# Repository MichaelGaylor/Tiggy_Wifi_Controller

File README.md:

# Tiggy WiFi CNC Motion Controller

Open-source ESP32 **6-axis** CNC motion controller firmware with LinuxCNC and GRBL support. Free and fully functional for all 6 axes with LinuxCNC, GRBL senders, or any G-code host. Mach3 support available separately.

Replaces parallel port drivers with a WiFi or Ethernet-connected motion controller supporting up to 6 axes, spindle encoder feedback, and expanded I/O. Works standalone (GRBL-compatible serial/telnet), with LinuxCNC, or with Mach3 (plugin sold separately). **All 6 axes are free and open source** -- the only limitation is in the Mach3 plugin, which requires a Pro Mach3 license for axes 4-6.

## Downloads

| Component | Download | Description |
|-----------|----------|-------------|
| **ESP32 Firmware** | [Flash from browser](https://michaelgaylor.github.io/Tiggy_Wifi_Controller/) | One-click web flasher (Chrome/Edge) |
| **LinuxCNC** | [Tiggy-LinuxCNC.tar.gz](https://github.com/MichaelGaylor/Tiggy_Wifi_Controller/releases/latest/download/Tiggy-LinuxCNC.tar.gz) | Driver, installer and set-up wizard |
| **Mach3 Plugin** | [www.tiggyengineering.com](https://www.tiggyengineering.com) | Windows plugin (free: 3-axis, Pro: 6-axis) |
| **Protocol Tester** | [TiggyProtocolTester.exe](https://github.com/MichaelGaylor/Tiggy_Wifi_Controller/releases/latest/download/TiggyProtocolTester.exe) | Windows GUI for testing and configuring |

Firmware and LinuxCNC builds are created automatically via GitHub Actions.

## Features

- Up to **6 axes** (X, Y, Z, A, B, C) with independent step/direction control
- **WiFi or Ethernet** (W5500) connectivity -- auto-detected, no configuration needed
- Motion streamed from the host as timed segments with acknowledgement: evenly spaced pulses, and lost or repeated packets can never lose or repeat a step
- Safe when the host goes away: host watchdog, jog deadman, outputs off on E-stop
- GRBL-compatible serial/telnet interface for standalone use
- Homing, limit switches, E-stop and probe inputs, handled in the controller
- Spindle on/off or PWM, charge pump, auxiliary outputs and inputs (count varies by board)
- Spindle speed feedback from an encoder or a one-pulse-per-revolution sensor
- **Screw cutting on lathes**: the controller itself keeps the tool in step with the spindle, so the pitch holds when the spindle slows in the cut and every pass follows the last
- Optional **I/O expansion module** (pendant buttons, relay outputs)
- Auto-discovery and automatic reconnection

## Supported Hardware

| Board | MCU | Wired Axes | Notes |
|-------|-----|------------|-------|
| Tiggy Standard board | ESP32-S3-Zero (FH4R2) | 3 (X/Y/Z) | Compact, Quad SPI PSRAM |
| Tiggy Pro board (Octal) | ESP32-S3-DevKitC-1 (N16R8/N8R8) | 6 (X/Y/Z/A/B/C) | Octal SPI PSRAM, limited I/O |
| Tiggy Pro board (Quad) | ESP32-S3-DevKitC-1 (N8/N8R2) | 6 (X/Y/Z/A/B/C) | Quad SPI PSRAM, more I/O |
| Classic board | ESP32-WROOM-32 | 6 (limited I/O) | Legacy support |

All boards run the same 6-axis firmware. "Wired Axes" refers to the number of step/dir GPIO pairs physically routed on the board. The firmware supports 6 axes regardless of board -- unused axes simply have no GPIO assigned.

One setting trades the B and C axes of the six-axis boards for inputs and outputs - a spindle sensor, a charge pump, more auxiliary I/O: see [Four axes and more I/O](#four-axes-and-more-io-spindle-sensor-and-screw-cutting).

## Quick Start

### Flash Firmware

**Easiest:** Open the [Web Flasher](https://michaelgaylor.github.io/Tiggy_Wifi_Controller/) in Chrome or Edge, plug in your ESP32 via USB, select your board, and click Flash. No software install needed.

**From source** (requires [PlatformIO](https://platformio.org/)):

```bash
cd firmware
pio run -e esp32s3-devkitc -t upload    # Tiggy Pro board (6 wired axes)
pio run -e esp32s3-zero -t upload       # Tiggy Standard board (3 wired axes)
```

### LinuxCNC

```bash
sudo apt install linuxcnc-uspace linuxcnc-uspace-dev   # already there on the LinuxCNC live image
tar xzf Tiggy-LinuxCNC.tar.gz
cd linuxcnc-package
./install.sh    # builds the driver, then starts the set-up program
```

Or double-click `install.desktop` from your file manager.

The set-up program ("Tiggy set-up for LinuxCNC" in the menu afterwards) finds the controller on the network and sets up a mill, router or lathe with it connected, in the manner of Mach3's Config menu: which axis each motor output drives, motor tuning with the motor running from the page, switches with a lamp for each input, the spindle and its sensor. It writes a complete configuration to `~/linuxcnc/configs` and starts LinuxCNC with it. No realtime kernel is needed: LinuxCNC plans the motion and the controller makes the step pulses. What to expect, and every pin and setting of the `tiggy` driver, is in [linuxcnc/README.md](linuxcnc/README.md).

### Mach3 (Windows)

Download the Mach3 plugin from [www.tiggyengineering.com](https://www.tiggyengineering.com), then:

1. Copy `Tiggy.dll` to `C:\Mach3\PlugIns\` and `M62-M65.m1s` to `C:\Mach3\macros\Mach3Mill\`
2. Start Mach3 and choose **Tiggy Motion Controller** as the motion device
3. Set the machine up in Mach3's own Config menu (Motor Tuning, Ports and Pins, Homing/Limits) -- the plugin finds the controller by itself

Plugin 2.0 needs controller firmware 1.2.0 or newer. See the [User Manual](Tiggy_Plugin_Manual.md).

**Free tier**: 3 axes (X/Y/Z). **Pro Mach3 license**: 6 axes, slaved axes, I/O expansion module, screw cutting (G32/G76 in Mach3 Turn). Note: this axis limit applies **only to the Mach3 plugin**. LinuxCNC, GRBL senders, and all other host software get full 6-axis support for free.

## Four axes and more I/O: spindle sensor and screw cutting

Six axes use nearly every terminal of a Tiggy Pro board. A lathe that cuts threads, and many a mill, would rather have four axes and the inputs and outputs. Setting the controller's *machine layout* to **four axes** (configuration key `WCNC_CFG_MACHINE_LAYOUT`; in Mach3 it is on the plugin's Terminals tab) keeps X, Y, Z and A - and Ethernet - and turns the terminals of B and C into inputs and outputs. The same set-up serves a lathe and a mill: the spindle sensor takes only the inputs its kind needs, and every sensor terminal it leaves free is an auxiliary input.

With four axes ("or" = what the terminal is when the sensor does not use it):

| | Tiggy Pro (octal memory) | Tiggy Pro (quad memory) |
|---|---|---|
| Encoder A | GPIO 16, or auxiliary input 3 | GPIO 16, or auxiliary input 4 |
| Encoder B | GPIO 17, or auxiliary input 4 | GPIO 17 |
| Index pulse / single sensor | GPIO 21, or auxiliary input 2 | GPIO 37 |
| Other auxiliary inputs | 1: GPIO 18 | 1 to 3: GPIO 18, 21, 36 |
| Auxiliary outputs | 1 to 3: GPIO 11, 12, 40 | 1 to 5: GPIO 11, 12, 40, 39, 34 |
| Charge pump | GPIO 39 | GPIO 10 |

So an octal-memory Pro board with four axes, Ethernet and an encoder with index still has a limit/home input per axis, probe, E-stop, an auxiliary input, the spindle output, a charge pump and three auxiliary outputs; without a sensor it has four auxiliary inputs. No terminal changes between input and output with the sensor setting - the sensor only ever shares a terminal with an input - so a sensor left wired while the setting is changed is never driven against. A single sensor has its terminal even with six axes on both Pro boards (GPIO 21 and GPIO 37). The Tiggy Standard board has its sensor terminals in any case (encoder A / B / index on GPIO 15 / 16 / 17; those the sensor does not use are auxiliary inputs 1 to 3). `firmware/test/test_pin_layout.c` checks every combination for each board and prints it.

The spindle sensor is either an **encoder with A and B channels**, with or without an index pulse (100 lines or more), or a **single sensor giving one pulse per revolution**, which goes on the index terminal. The encoder gives the better thread: with one pulse per turn the controller cannot see a change of spindle speed until the turn is over. (A single sensor giving several pulses per revolution serves the speed display only: nothing tells the pulses apart, so no thread can be started by them.) The inputs have the chip's weak pull-ups: a single sensor that switches to ground connects directly, but an open-collector encoder needs pull-up resistors of its own (a few kilohms to 3.3 V) to be read at speed, or push-pull outputs.

A threading pass is played in step with the spindle or not at all. If something breaks into one - a feed hold or stop from the host in the middle of it, the host leaving the controller without motion, a spindle the axes cannot keep up with - the controller brings the axes to rest, drops what was left and says so (`WCNC_STREAM_SYNC_LOST`), rather than carry on out of step with the thread already cut.

Screw cutting is available to both hosts: G32 and G76 in Mach3 Turn through the plugin, G33 and G76 in LinuxCNC through its driver (`linuxcnc/README.md`).

For screw cutting the host streams the threading pass like any other move, marked to be played *by the spindle* and to begin at its index (`WCNC_SEG_FLAG_SPINDLE_SYNC`, `WCNC_SEG_FLAG_INDEX_START` in `protocol/wifi_cnc_protocol.h`). The controller then advances through the move by the angle the spindle really turns, so the pitch does not depend on the spindle holding its speed, a spindle that stalls stops the axes with it, and every pass begins at the same place on the work. The Mach3 plugin does this for G32 and G76 in Mach3 Turn, the LinuxCNC driver for G33 and G76.

### A carrier board for either layout

[`hardware/devkitc-carrier`](hardware/devkitc-carrier) is a KiCad project for a board that an ESP32-S3-DevKitC-1 plugs into. It has plugs for six drives, and four jumpers that give the pins of B and C either to their drives (six axes) or to three relays and the charge pump (four axes). Also on it: a socket for a W5500 Ethernet module, seven opto-isolated inputs (limits, E-stop, probe), a separate plug for the spindle sensor and a 0 to 10 V spindle speed output. It is revision A and has not been built yet - see its README before ordering one.

## Architecture

```
Mach3 / LinuxCNC / Serial Terminal
              |
         [TCP:58429 + UDP:58427/58428]
              |
        ESP32-S3 Firmware (this repo)
              |
        Step/Dir/Enable/Spindle/IO GPIO
```

- **TCP** (port 58429): Handshake, configuration, keep-alive
- **UDP** (port 58427): Motion stream, jog, home, outputs, E-stop; status reports go back to the host
- **Protocol**: Defined in `protocol/wifi_cnc_protocol.h` (version 1.2)

## Testing without hardware

The firmware's motion code (`firmware/main/motion`) is plain C that also builds on a PC, where it runs behind the real network ports with a simulated machine attached:

```bash
firmware/test/pc/build.sh                 # or build.bat on Windows: builds the test library, runs the unit test
python tools/firmware_sim.py              # the firmware's motion code as a controller on this PC
python tools/protocol_conformance.py --sim --motion 127.0.0.1    # protocol tests
python tools/firmware_selftest.py         # G-code mode moves, feed hold, homing, older hosts, starved stream, pulse spacing
python tools/threading_test.py            # screw cutting: every step of a pass against the angle of a simulated spindle
python tools/encoder_bench_test.py 127.0.0.1 --lines 1024 --sim    # the bench test of a real encoder (below), the simulator turning one
python tools/encoder_loopback_test.py 127.0.0.1 --sim              # the board's test of its own encoder inputs (below), on the simulator
python tools/ugs_compat_test.py           # TiggyUGS's own connection, planner and sender code against the firmware
                                          # (needs TiggyUGS's source and its Python packages: see the file)
```

Host software (the Mach3 plugin, LinuxCNC, TiggyUGS) connects to it like to a board. Hosts written for protocol 1.0 or 1.1 keep working with firmware 1.2: their speed-described segments are played as before, the status report shows them the room in the queue those wait in, and their reset packet stops and drops what they sent. `tools/tiggy_sim.py` is an independent model of the same protocol in Python; the conformance tests hold both to one behaviour, and can be run against a real board too (`protocol_conformance.py <ip>`, add `--motion` only when the motors are free to move).

The LinuxCNC driver is tested the same way. It builds, unchanged, around a stand-in for LinuxCNC and is run against the firmware simulator (it starts its own simulators, so close one you started by hand first):

```bash
linuxcnc/test/build.sh                    # or build.bat on Windows
python tools/linuxcnc_driver_test.py      # moves to the step, packet loss, a stalling PC, E-stop, limits, reconnection
linuxcnc/test/run_in_linuxcnc.sh          # the same driver inside a real LinuxCNC (Linux with linuxcnc-uspace-dev):
                                          # a mill, home switches, G33, and a lathe with G33 and a G76 cycle (also at 150 rpm by a one-pulse sensor)
xvfb-run -a python3 linuxcnc/test/config_test.py     # the set-up program, worked from its pages against the simulator
```

### With a board on the bench

A bare dev board is enough; nothing needs to be wired to it.

```bash
python tools/protocol_conformance.py <ip> --motion    # the binary protocol over the network (the axes "move": no motors, or a free machine)
python tools/grbl_serial_test.py COM14                # the G-code interface on the USB port: moves, arcs, hold, jog and jog cancel, reset, no drift
python tools/grbl_serial_test.py <ip>                 # the same interface over the network (telnet, port 23)
python tools/ugs_serial_test.py COM14                 # TiggyUGS's own serial connection and sender against it (needs TiggyUGS's source)
python tools/latency_test.py <ip>                     # how promptly the controller answers over the network: median and worst case
linuxcnc/test/run_on_board.sh <ip> --motion           # LinuxCNC itself driving the board (on Linux, or in Windows under WSL): homing, MDI,
                                                      # a program, jogging, abort, E-stop and a long run, each checked to the step
```

With one wire on it - X step linked to the single spindle sensor's terminal, GPIO 1 to GPIO 21 on the DevKitC - the board tests its own step output, its spindle sensor input and screw cutting:

```bash
python tools/spindle_loopback_test.py <ip> --bench    # counts its own step pulses, then cuts threading passes against its spindle output
```

It changes settings (the spindle sensor, and which terminal is X step and which the spindle output) and puts them back at the end, so nothing but the wire may be connected to those two terminals. The file says what is measured and how.

With three links - spindle output to encoder A, charge pump to encoder B, Z step to the index input: GPIO 9 to 16, 39 to 17 and 42 to 21 on the DevKitC with octal memory - the board tests its encoder inputs with no encoder at all:

```bash
python tools/encoder_loopback_test.py <ip> --bench    # A, B and index made by the controller itself: the count at speed, the index pulse, screw cutting
```

The spindle PWM and the charge pump, set to one frequency, are an encoder's A and B; Z stepped by the clock is its index pulse, and a measure of the count as well, since all three come from one crystal. The test checks that the real pulse counter neither loses nor gains a count at up to 50 000 lines a second (200 000 counts, two and a half million in all; the spindle output makes no more than 50 kHz), that every index pulse is taken and found at one place, and that threading passes are played by A and B as they are by a single sensor. What it cannot check is an encoder itself and the wiring to it - for that:

A spindle encoder can be tested the same way before it is on a machine: wired to the controller, turned by hand, then spun with a cordless drill on its shaft.

```bash
python tools/encoder_bench_test.py <ip> --lines 600 --bench    # A, B and the index pulse read by hand, then threading passes by the drill-spun encoder
```

It says what to do next and beeps each time (`--say`: it speaks), and goes by what the controller sees, so there is no hurry. By hand it checks that A and B are counted both ways and that the index pulse comes once a turn at the same place in the count - which is the number of lines being right; if it is not, it says what the encoder looks like, and it names the wire if one is missing. With the drill it checks that no counts are lost at speed, that a pass lies where it should on the spindle and a second pass on the first, that Z stops with the spindle, and that a pass waits for a spindle at rest. It sets the four-axis terminal layout and the sensor settings and puts them back (`--keep`: leaves them), and steps the passes out on Z: no drive may be connected there. The inputs take 3.3 V and no more - the file says how each kind of encoder output is wired.

## Documentation

- [User Manual](https://michaelgaylor.github.io/Tiggy_Wifi_Controller/plugin_manual.html) -- full plugin configuration guide ([markdown](Tiggy_Plugin_Manual.md))
- [Engineering Reference](https://michaelgaylor.github.io/Tiggy_Wifi_Controller/engineering_reference.html) -- protocol, wiring diagrams, and internals

## License

MIT License -- see [LICENSE](LICENSE)

The ESP32 firmware, LinuxCNC HAL component, protocol definition, and tools are all open source and provide **full 6-axis support at no cost**. The Mach3 plugin is distributed separately -- its Free tier supports 3 axes; a Pro Mach3 license unlocks all 6 axes and additional features.

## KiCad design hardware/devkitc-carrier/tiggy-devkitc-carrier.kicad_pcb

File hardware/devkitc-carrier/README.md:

# Tiggy DevKitC carrier (revision A)

A carrier board for an **ESP32-S3-DevKitC-1** running the Tiggy firmware (environment `esp32s3-devkitc`, octal-memory modules such as N16R8), for either of the firmware's terminal layouts: **six axes**, or **four axes** with three relays, a charge pump and a spindle encoder. Four jumpers choose. KiCad 10 project, two layers, 182 x 95 mm.

> **Status: not yet built.** The schematic passes KiCad's electrical rule check and the routed board its design rule check (no violations, nothing unconnected, board and schematic in agreement), but no board has been made or powered. Check it against your own parts before ordering - above all the Ethernet module's pin order (below) and the relays.

## What is on it

| | |
|---|---|
| Controller | ESP32-S3-DevKitC-1 on two 22-pin sockets. A second row of holes takes the 25.4 mm wide boards sold under the same name. |
| Supply | 12 to 24 V DC (28 V is the regulator's absolute maximum), fused (resettable) and protected against reverse connection. A Recom R-78E5.0-1.0 makes 5 V; the DevKitC is fed through a diode, so its USB port never supplies the relays and the two supplies cannot fight. |
| Drives | Six plugs - X, Y, Z, A, B, C - each with STEP, DIR, EN and 0 V: 5 V push-pull outputs (74AHCT541 / 74AHCT125), a buffer of its own for every signal of every drive. B and C work with the jumpers set for six axes. |
| Jumpers | Four, side by side in the middle of the board: the B and C drives, or the relays and the charge pump ([below](#six-axes-or-four)). |
| Inputs | Seven opto-isolated inputs with an LED each: limit/home X, Y, Z, A, auxiliary input 1, E-stop, probe. A switch or an NPN sensor between the terminal and 0 V operates the input; the supply voltage is brought out for sensors. |
| Spindle sensor | Its own six-way plug: 5 V, 0 V, A, B, Z. Encoder with or without index, or a single sensor on Z. 5 V pull-ups (open-collector sensors connect directly), Schmitt triggers, good for the 250 000 lines a second the firmware reads. Without a sensor the three are auxiliary inputs 2 to 4. With six axes, A and B are the limit/home inputs of the B and C axes. |
| Outputs | Three relays (Omron G5LE-1, 5 V coil) on auxiliary outputs 1 to 3, each switched by a MOSFET so the coil gets its full 5 V; changeover contacts on three-way plugs, an LED each. With the jumpers set for four axes. |
| Spindle speed | The spindle PWM as 0 to 10 V for a frequency converter (needs 12 V or more at the supply terminal), and as a 5 V PWM signal. The charge pump output (four axes) is on the same plug. |
| Ethernet | Socket for a **USR-ES1** W5500 module (the "W5500 Lite", WIZ820io pin order). |

Plugs are Phoenix MC 1,5/..-G-3,81 (signals) and MSTBA 2,5/..-G-5,08 (supply, relays), or the many compatible "15EDG" parts.

## Six axes or four

The DevKitC has not the pins for six drives and for relays and an encoder as well, so the firmware has two terminal layouts, and six of the pins have a different job in each:

| DevKitC pin | Six axes | Four axes |
|---|---|---|
| GPIO 40 | B step | Relay 3 |
| GPIO 11 | B direction | Relay 1 |
| GPIO 39 | C step | Charge pump |
| GPIO 12 | C direction | Relay 2 |
| GPIO 16 | B limit/home (terminal A of the spindle sensor plug) | Encoder A, or auxiliary input 3 |
| GPIO 17 | C limit/home (terminal B of the spindle sensor plug) | Encoder B, or auxiliary input 4 |

The first four go through the jumper block (JP2 to JP5). Put **all four links towards `6 AXES`, or all four towards `4 AXES + RELAYS`**, and set the controller's terminal layout to the same: in the Mach3 plugin on the Terminals tab, otherwise with the protocol tester (`tools/protocol_test_gui.py`). The spindle sensor is chosen in the same place. A new controller is set for six axes.

Whichever side is not chosen is held off by pull-down resistors: with six axes the relays stay released and the charge pump terminal stays low; with four the B and C plugs are quiet.

If the links and the firmware do not agree nothing is damaged, but outputs do the wrong thing: links for six axes with the firmware on four puts the charge pump's square wave on the C drive's step input, and links for four with the firmware on six operates the relays whenever B or C moves. So set both before connecting anything to the B and C plugs or to the relays.

With six axes there is no charge pump, no relay and no encoder - the firmware has no pins left for them. A single sensor giving one pulse per turn still works, on terminal Z of the spindle sensor plug. The limit switches of B and C go on that plug's A and B terminals: a switch or an NPN sensor to 0 V, as on the other inputs, but these two are not opto-isolated.

## Which pin does what

| DevKitC pin | Function | | DevKitC pin | Function |
|---|---|---|---|---|
| GPIO 1 / 3 | X step / direction | | GPIO 5, 6, 7, 15 | Limit/home X, Y, Z, A |
| GPIO 2 / 4 | Y step / direction | | GPIO 18 | Auxiliary input 1 |
| GPIO 42 / 38 | Z step / direction | | GPIO 13 | E-stop |
| GPIO 41 / 10 | A step / direction | | GPIO 14 | Probe |
| GPIO 40 / 11 | B step / direction, or relays 3 and 1 | | GPIO 16, 17 | Encoder A, B (or auxiliary inputs 3, 4), or limit/home B, C |
| GPIO 39 / 12 | C step / direction, or charge pump and relay 2 | | GPIO 21 | Index / single sensor (or auxiliary input 2) |
| GPIO 8 | Drive enable | | GPIO 9 | Spindle PWM |
| GPIO 45, 46, 0, 47 | Ethernet MOSI, MISO, clock, interrupt | | | |

These are the firmware's own maps (`firmware/main/pin_config.h`, `pin_layout.c`) for its two terminal layouts, so no pin numbers have to be entered: only the layout is chosen.

## Four things done on purpose

- **Every drive's enable has a buffer of its own.** The firmware has one enable pin for all the drives, but a drive's enable input takes some 10 mA, and six of them are more than one logic output is rated for.
- **The Ethernet module is selected only after the ESP32 has left reset** (Q1, some 20 to 80 ms after the reset line goes high - long after the boot options are read, long before the firmware first talks to the module). The firmware has no pin for the module's chip select and expects it tied to 0 V. Tied there directly, the module drives its data output onto GPIO 46 all the time, and GPIO 46 is one of the pins the ESP32 reads as a boot option: left high it can stop the board entering download mode through the UART port. Solder jumper JP1 ties chip select to 0 V directly if you prefer the plain arrangement. The module's reset follows the ESP32's.
- **GPIO 0 has a pull-up** (4.7 k). It is the Ethernet clock, and the DevKitC has no pull-up of its own on it - only the one inside the chip - while it must be high at reset.
- **The outputs to the drives are held low while the ESP32 is in reset** (10 k on every buffer input), so no stray steps at power-on.

## Limits of this revision

- Relay contacts are laid out for **low voltage only** (tracks 1.2 mm, 1 mm clearance). Switch mains with an external relay or contactor.
- The spindle sensor inputs need a **74LVC14** (U4). A 74HC14 fits the footprint but is not 5 V tolerant on a 3.3 V supply.
- With six axes the limit/home inputs of B and C are the spindle sensor's inputs: protected like them (24 V on a terminal does no harm), but not opto-isolated.
- A short on the 5 V sensor supply resets the board (the regulator limits the current); there is no separate fuse for it.
- With USB alone the ESP32 runs, but the drive outputs, relays and inputs need the 12-24 V supply.

## How the project is made

Everything is generated from [`gen/design.py`](gen/design.py), which holds the circuit (every part, every net) and where each part sits:

```
python gen/build.py --tracklayer path/to/Tracklayer
```

writes the project's own library (the two module sockets), the schematic, runs KiCad's electrical rule check, exports the netlist and compares it with `design.py`, places the parts on the board from that netlist, routes it with [Tracklayer](https://github.com/MichaelGaylor/Tracklayer), fills the copper pours, joins with a via any patch of the 0 V pour that the tracks have cut off from the rest, and runs KiCad's design rule check with the schematic compared against the board. The build ends with an error if any of the checks finds a fault. Reports are written to `build/`. It needs KiCad 10 (`kicad-cli` and the Python that comes with it; where KiCad is not in `C:\Program Files\KiCad\10.0`, set `KICAD_BIN` and `KICAD_SHARE` to its `bin` and `share/kicad` directories) and takes about twenty minutes, nearly all of it routing. `--keep-routing` reuses the last routing when no pad has moved and nothing is connected differently.

The schematic has a page for each function - controller, supply, drives, the B and C drives with the jumpers, drive enable, inputs, spindle sensor, relays, spindle speed, Ethernet - each drawn as a circuit, with wires. A name in a pointed box is a signal that goes to another page; the page it goes to is written beside it. Where each part is drawn is in [`gen/gen_sch.py`](gen/gen_sch.py); what it is connected to stays in `design.py`, and the build fails if the drawing and `design.py` ever disagree about a single pin. Hand edits to a `.kicad_sch` or to the `.kicad_pcb` are lost at the next build: change the two files in `gen/`, or stop using the generator and carry on in KiCad.

Dimensions used for the sockets: Espressif's drawing of the ESP32-S3-DevKitC-1 v1.1 (25.40 x 62.74 mm, rows 22.86 mm apart, last pin 8.00 mm from the USB end) and USR IOT's data sheet of the USR-ES1 (two rows of six pins 20.32 mm apart; left row seen from above with the socket away from you: GND, GND, MOSI, SCLK, SCS, INT; right row: GND, 3.3 V, 3.3 V, NC, RST, MISO).

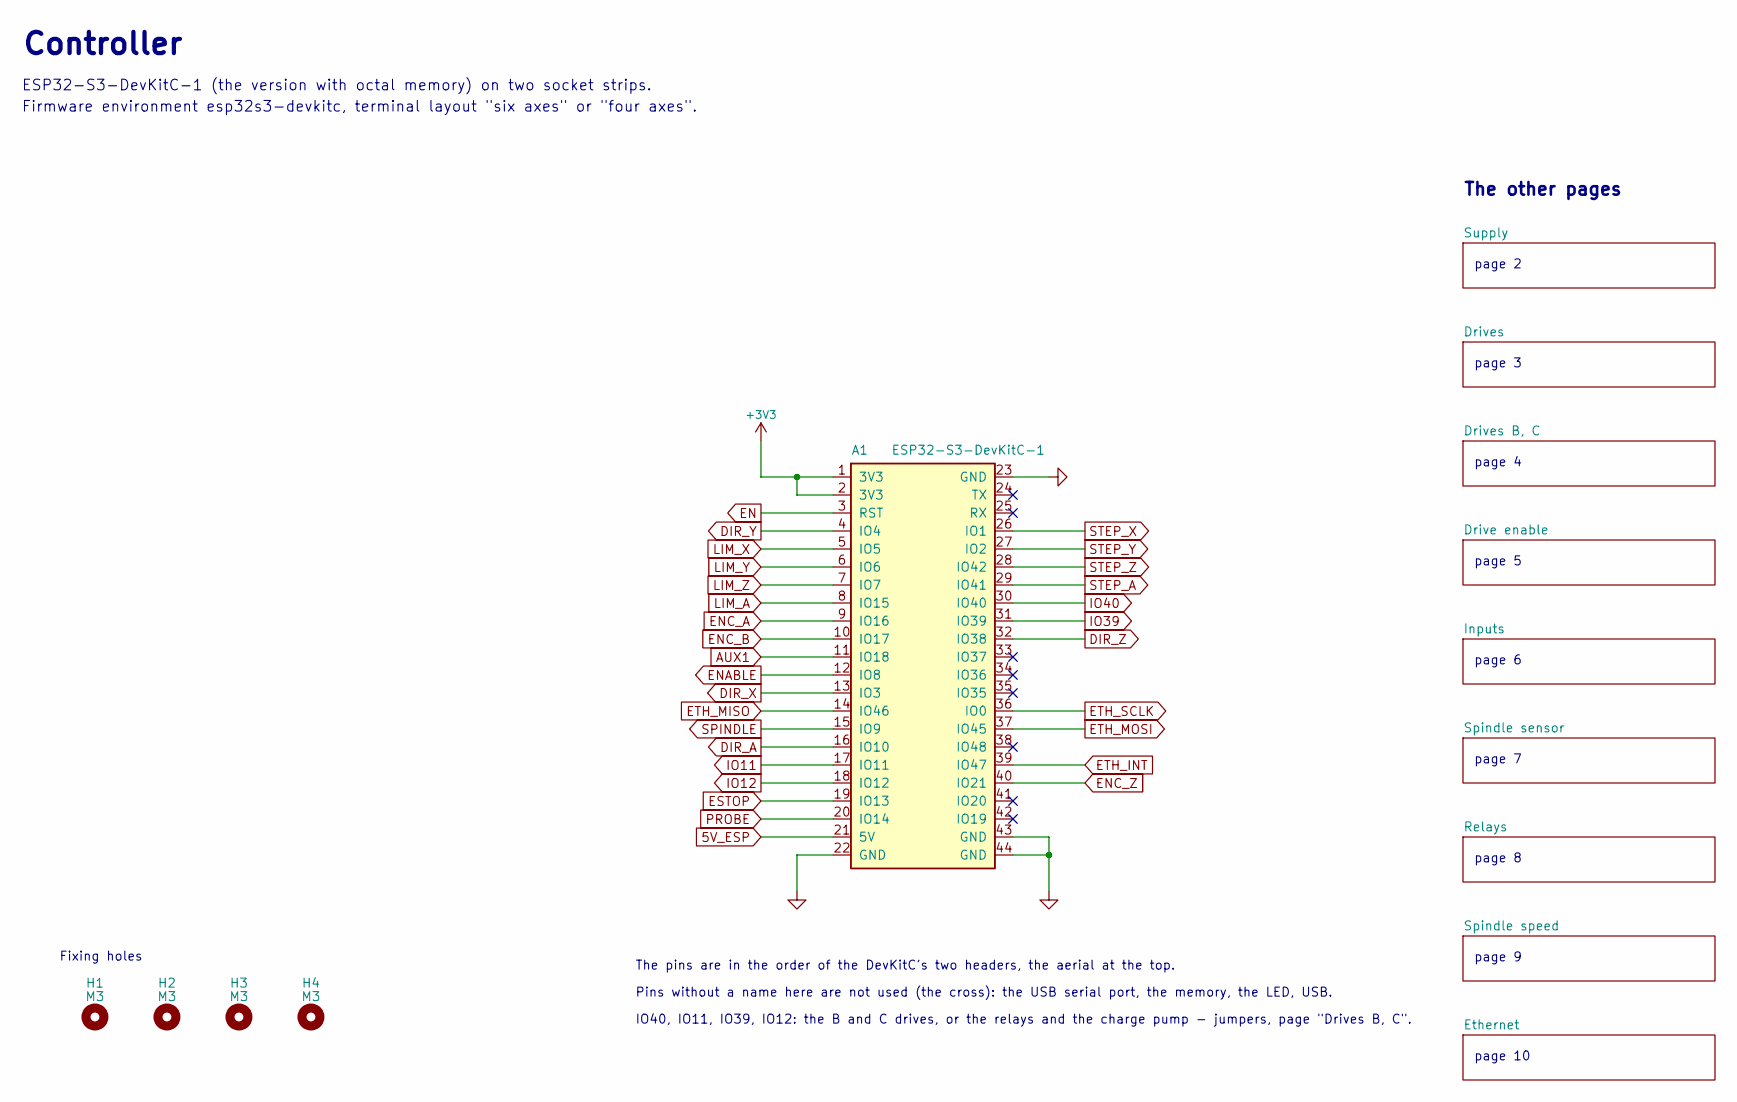
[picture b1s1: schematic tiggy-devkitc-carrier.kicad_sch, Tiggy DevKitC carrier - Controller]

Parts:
A1: ESP32-S3-DevKitC-1; ESP32-S3-DevKitC-1_Socket
H1, H2, H3, H4: M3; MountingHole_3.2mm_M3

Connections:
5V_ESP: A1.21 (5V); also elsewhere on the board
+3V3: A1.1 (3V3), A1.2 (3V3); also elsewhere on the board
AUX1: A1.11 (IO18); also elsewhere on the board
DIR_A: A1.16 (IO10); also elsewhere on the board
DIR_X: A1.13 (IO3); also elsewhere on the board
DIR_Y: A1.4 (IO4); also elsewhere on the board
DIR_Z: A1.32 (IO38); also elsewhere on the board
EN: A1.3 (RST); also elsewhere on the board
ENABLE: A1.12 (IO8); also elsewhere on the board
ENC_A: A1.9 (IO16); also elsewhere on the board
ENC_B: A1.10 (IO17); also elsewhere on the board
ENC_Z: A1.40 (IO21); also elsewhere on the board
ESTOP: A1.19 (IO13); also elsewhere on the board
ETH_INT: A1.39 (IO47); also elsewhere on the board
ETH_MISO: A1.14 (IO46); also elsewhere on the board
ETH_MOSI: A1.37 (IO45); also elsewhere on the board
ETH_SCLK: A1.36 (IO0); also elsewhere on the board
GND: A1.22 (GND), A1.23 (GND), A1.43 (GND), A1.44 (GND); also elsewhere on the board
IO11: A1.17 (IO11); also elsewhere on the board
IO12: A1.18 (IO12); also elsewhere on the board
IO39: A1.31 (IO39); also elsewhere on the board
IO40: A1.30 (IO40); also elsewhere on the board
LIM_A: A1.8 (IO15); also elsewhere on the board
LIM_X: A1.5 (IO5); also elsewhere on the board
LIM_Y: A1.6 (IO6); also elsewhere on the board
LIM_Z: A1.7 (IO7); also elsewhere on the board
PROBE: A1.20 (IO14); also elsewhere on the board
SPINDLE: A1.15 (IO9); also elsewhere on the board
STEP_A: A1.29 (IO41); also elsewhere on the board
STEP_X: A1.26 (IO1); also elsewhere on the board
STEP_Y: A1.27 (IO2); also elsewhere on the board
STEP_Z: A1.28 (IO42); also elsewhere on the board

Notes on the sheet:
The pins are in the order of the DevKitC's two headers, the aerial at the top.
Pins without a name here are not used (the cross): the USB serial port, the memory, the LED, USB.
IO40, IO11, IO39, IO12: the B and C drives, or the relays and the charge pump - jumpers, page "Drives B, C".
Fixing holes
The other pages
page 2
page 3
page 4
page 5
page 6
page 7
page 8
page 9
page 10
Controller
ESP32-S3-DevKitC-1 (the version with octal memory) on two socket strips.
Firmware environment esp32s3-devkitc, terminal layout "six axes" or "four axes".

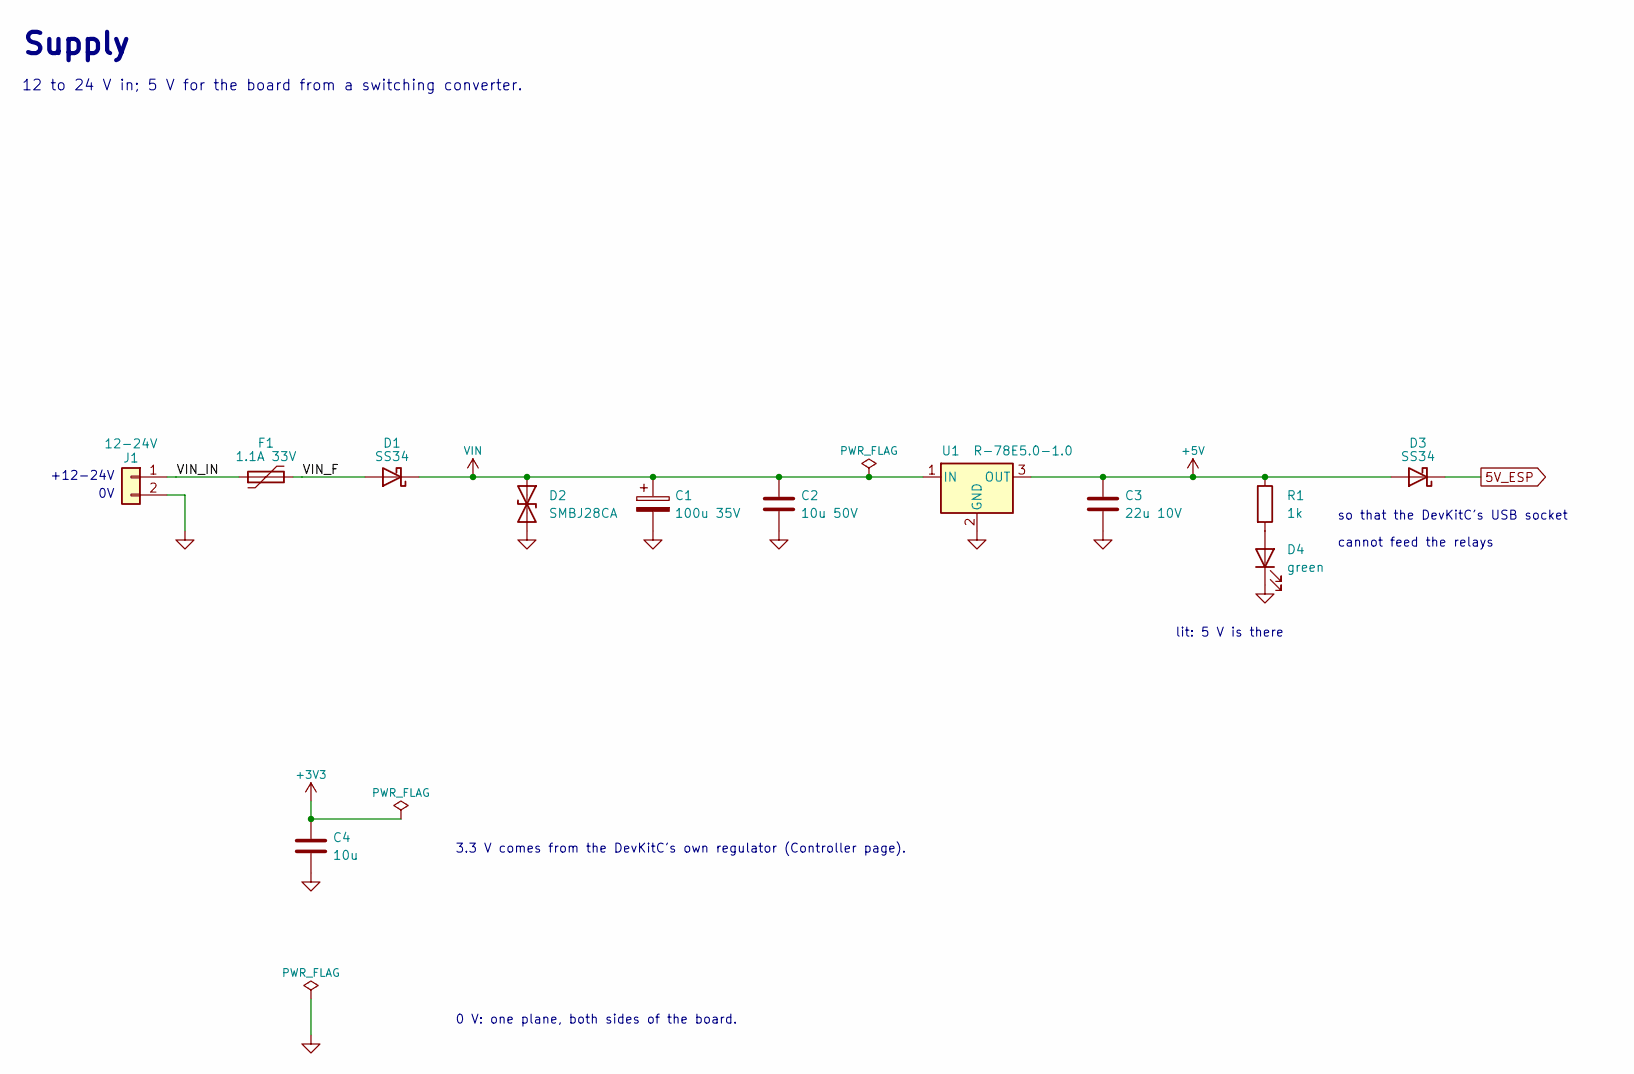
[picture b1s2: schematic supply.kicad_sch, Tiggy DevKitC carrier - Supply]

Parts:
C1: 100u 35V; CP_Radial_D8.0mm_P3.50mm
C2: 10u 50V; C_1206_3216Metric
C3: 22u 10V; C_1206_3216Metric
C4: 10u; C_1206_3216Metric
D1, D3: SS34; D_SMA
D2: SMBJ28CA; D_SMB
D4: green; LED_0805_2012Metric
F1: 1.1A 33V; Fuse_1812_4532Metric
J1: 12-24V; PhoenixContact_MSTBA_2,5_2-G-5,08_1x02_P5.08mm_Horizontal
R1: 1k; R_0603_1608Metric
U1: R-78E5.0-1.0; Converter_DCDC_RECOM_R-78E-0.5_THT

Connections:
5V_ESP: D3.1 (K); also elsewhere on the board
+3V3: C4.1; also elsewhere on the board
+5V: C3.1, D3.2 (A), R1.1, U1.3 (OUT); also elsewhere on the board
/Supply/VIN_F: D1.2 (A), F1.2
/Supply/VIN_IN: F1.1, J1.1
GND: C1.2, C2.2, C3.2, C4.2, D2.2 (A2), D4.1 (K), J1.2, U1.2 (GND); also elsewhere on the board
unnamed: D4.2 (A), R1.2
VIN: C1.1, C2.1, D1.1 (K), D2.1 (A1), U1.1 (IN); also elsewhere on the board

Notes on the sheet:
+12-24V
lit: 5 V is there
so that the DevKitC's USB socket
cannot feed the relays
3.3 V comes from the DevKitC's own regulator (Controller page).
0 V: one plane, both sides of the board.
Supply
12 to 24 V in; 5 V for the board from a switching converter.

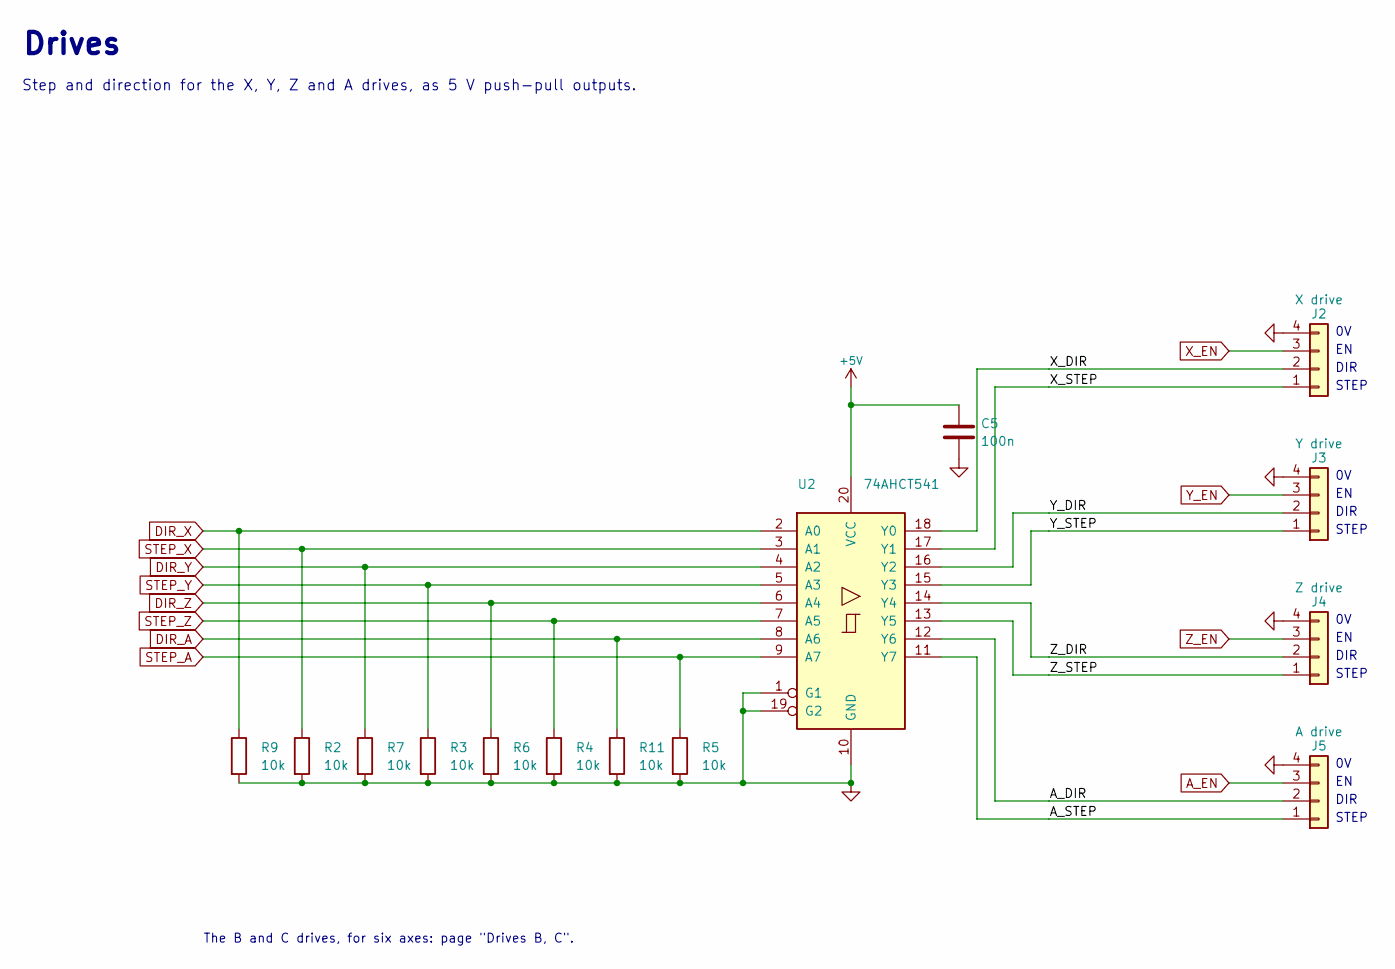
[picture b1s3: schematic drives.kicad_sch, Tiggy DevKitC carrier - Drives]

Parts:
C5: 100n; C_0603_1608Metric
J2: X drive; PhoenixContact_MC_1,5_4-G-3.81_1x04_P3.81mm_Horizontal
J3: Y drive; PhoenixContact_MC_1,5_4-G-3.81_1x04_P3.81mm_Horizontal
J4: Z drive; PhoenixContact_MC_1,5_4-G-3.81_1x04_P3.81mm_Horizontal
J5: A drive; PhoenixContact_MC_1,5_4-G-3.81_1x04_P3.81mm_Horizontal
R2, R3, R4, R5, R6, R7, R9, R11: 10k; R_0603_1608Metric
U2: 74AHCT541; SOIC-20W_7.5x12.8mm_P1.27mm

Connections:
+5V: C5.1, U2.20 (VCC); also elsewhere on the board
/Drives/A_DIR: J5.2, U2.12 (Y6)
/Drives/A_STEP: J5.1, U2.11 (Y7)
/Drives/X_DIR: J2.2, U2.18 (Y0)
/Drives/X_STEP: J2.1, U2.17 (Y1)
/Drives/Y_DIR: J3.2, U2.16 (Y2)
/Drives/Y_STEP: J3.1, U2.15 (Y3)
/Drives/Z_DIR: J4.2, U2.14 (Y4)
/Drives/Z_STEP: J4.1, U2.13 (Y5)
A_EN: J5.3; also elsewhere on the board
DIR_A: R11.1, U2.8 (A6); also elsewhere on the board
DIR_X: R9.1, U2.2 (A0); also elsewhere on the board
DIR_Y: R7.1, U2.4 (A2); also elsewhere on the board
DIR_Z: R6.1, U2.6 (A4); also elsewhere on the board
GND: C5.2, J2.4, J3.4, J4.4, J5.4, R2.2, R3.2, R4.2, R5.2, R6.2, R7.2, R9.2, R11.2, U2.1 (G1), U2.10 (GND), U2.19 (G2); also elsewhere on the board
STEP_A: R5.1, U2.9 (A7); also elsewhere on the board
STEP_X: R2.1, U2.3 (A1); also elsewhere on the board
STEP_Y: R3.1, U2.5 (A3); also elsewhere on the board
STEP_Z: R4.1, U2.7 (A5); also elsewhere on the board
X_EN: J2.3; also elsewhere on the board
Y_EN: J3.3; also elsewhere on the board
Z_EN: J4.3; also elsewhere on the board

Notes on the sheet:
STEP
DIR
The B and C drives, for six axes: page "Drives B, C".
Drives
Step and direction for the X, Y, Z and A drives, as 5 V push-pull outputs.

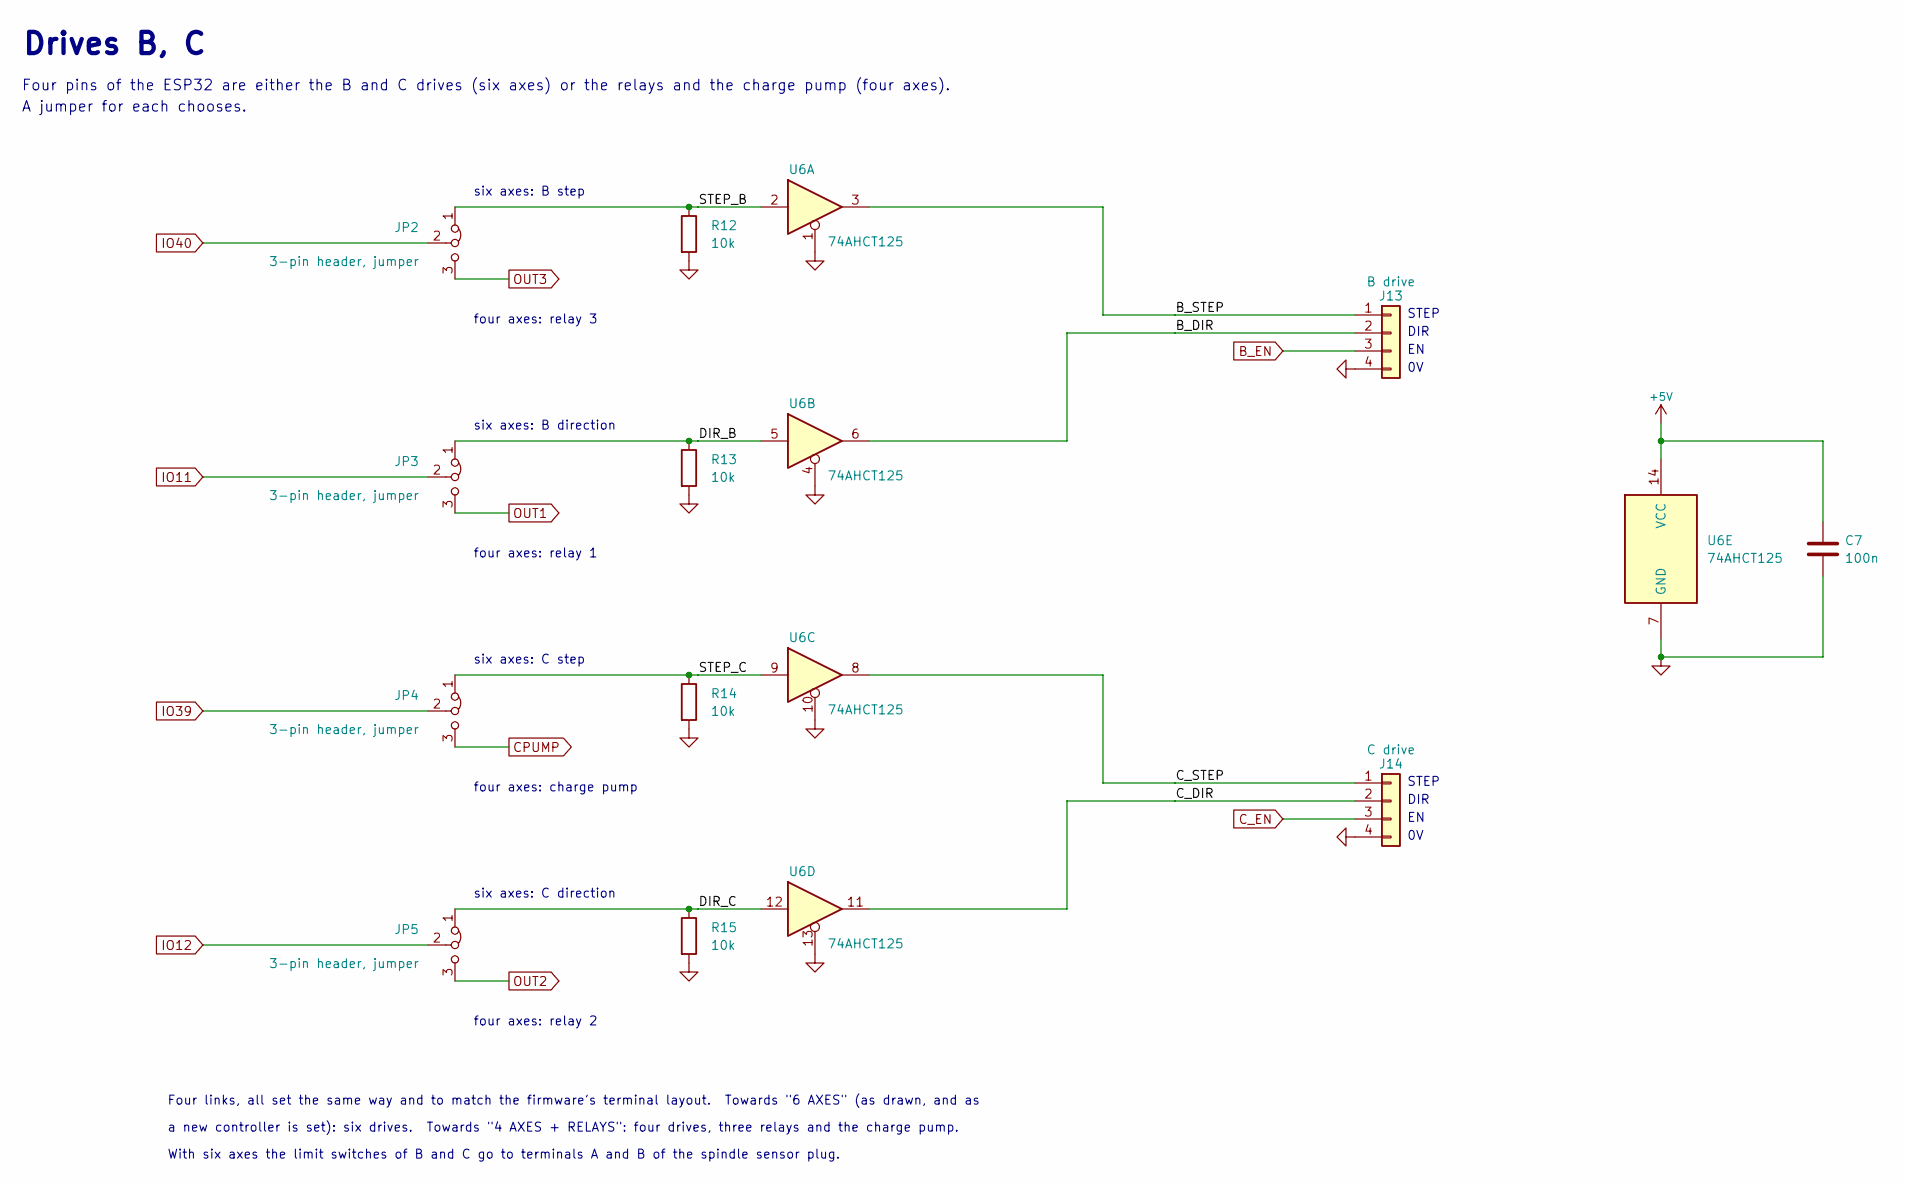
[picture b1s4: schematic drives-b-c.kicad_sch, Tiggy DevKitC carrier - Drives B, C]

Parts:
C7: 100n; C_0603_1608Metric
J13: B drive; PhoenixContact_MC_1,5_4-G-3.81_1x04_P3.81mm_Horizontal
J14: C drive; PhoenixContact_MC_1,5_4-G-3.81_1x04_P3.81mm_Horizontal
JP2, JP3, JP4, JP5: 3-pin header, jumper; PinHeader_1x03_P2.54mm_Vertical
R12, R13, R14, R15: 10k; R_0603_1608Metric
U6: 74AHCT125; SOIC-14_3.9x8.7mm_P1.27mm

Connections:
+5V: C7.1, U6.14 (VCC); also elsewhere on the board
/Drives B, C/B_DIR: J13.2, U6.6
/Drives B, C/B_STEP: J13.1, U6.3
/Drives B, C/C_DIR: J14.2, U6.11
/Drives B, C/C_STEP: J14.1, U6.8
/Drives B, C/DIR_B: JP3.1 (A), R13.1, U6.5
/Drives B, C/DIR_C: JP5.1 (A), R15.1, U6.12
/Drives B, C/STEP_B: JP2.1 (A), R12.1, U6.2
/Drives B, C/STEP_C: JP4.1 (A), R14.1, U6.9
B_EN: J13.3; also elsewhere on the board
CPUMP: JP4.3 (B); also elsewhere on the board
C_EN: J14.3; also elsewhere on the board
GND: C7.2, J13.4, J14.4, R12.2, R13.2, R14.2, R15.2, U6.1, U6.4, U6.7 (GND), U6.10, U6.13; also elsewhere on the board
IO11: JP3.2 (C); also elsewhere on the board
IO12: JP5.2 (C); also elsewhere on the board
IO39: JP4.2 (C); also elsewhere on the board
IO40: JP2.2 (C); also elsewhere on the board
OUT1: JP3.3 (B); also elsewhere on the board
OUT2: JP5.3 (B); also elsewhere on the board
OUT3: JP2.3 (B); also elsewhere on the board

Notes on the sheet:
six axes: B step
four axes: relay 3
six axes: B direction
four axes: relay 1
six axes: C step
four axes: charge pump
six axes: C direction
four axes: relay 2
STEP
DIR
Four links, all set the same way and to match the firmware's terminal layout. Towards "6 AXES" (as drawn, and as
a new controller is set): six drives. Towards "4 AXES + RELAYS": four drives, three relays and the charge pump.
With six axes the limit switches of B and C go to terminals A and B of the spindle sensor plug.
Drives B, C
Four pins of the ESP32 are either the B and C drives (six axes) or the relays and the charge pump (four axes).
A jumper for each chooses.

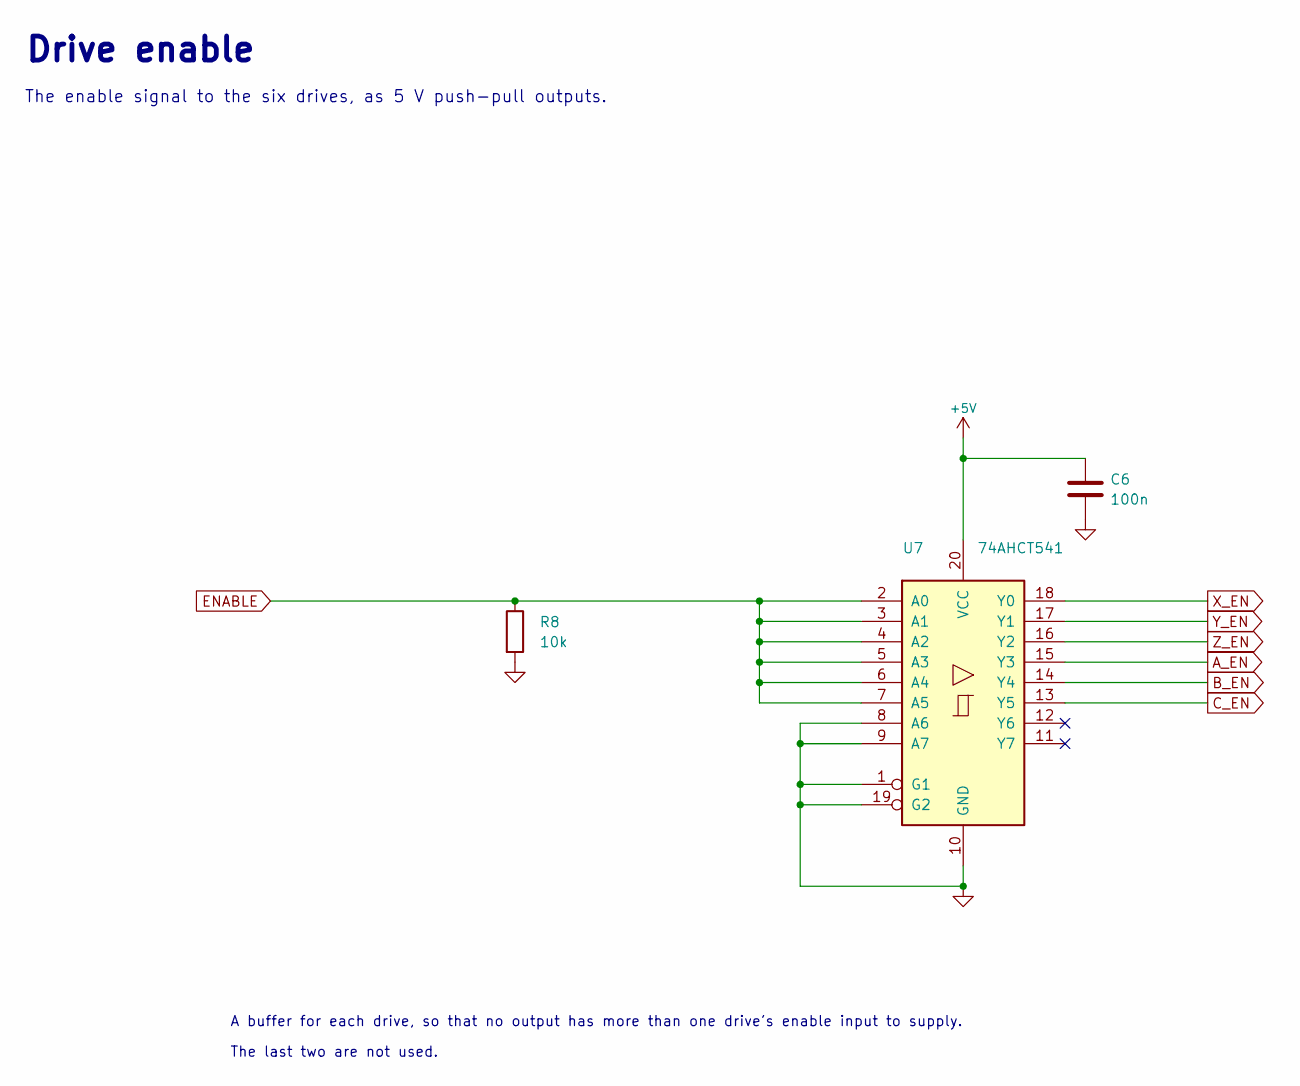
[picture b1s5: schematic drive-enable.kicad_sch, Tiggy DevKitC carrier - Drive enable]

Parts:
C6: 100n; C_0603_1608Metric
R8: 10k; R_0603_1608Metric
U7: 74AHCT541; SOIC-20W_7.5x12.8mm_P1.27mm

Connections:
+5V: C6.1, U7.20 (VCC); also elsewhere on the board
A_EN: U7.15 (Y3); also elsewhere on the board
B_EN: U7.14 (Y4); also elsewhere on the board
C_EN: U7.13 (Y5); also elsewhere on the board
ENABLE: R8.1, U7.2 (A0), U7.3 (A1), U7.4 (A2), U7.5 (A3), U7.6 (A4), U7.7 (A5); also elsewhere on the board
GND: C6.2, R8.2, U7.1 (G1), U7.8 (A6), U7.9 (A7), U7.10 (GND), U7.19 (G2); also elsewhere on the board
X_EN: U7.18 (Y0); also elsewhere on the board
Y_EN: U7.17 (Y1); also elsewhere on the board
Z_EN: U7.16 (Y2); also elsewhere on the board

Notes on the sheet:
A buffer for each drive, so that no output has more than one drive's enable input to supply.
The last two are not used.
Drive enable
The enable signal to the six drives, as 5 V push-pull outputs.
